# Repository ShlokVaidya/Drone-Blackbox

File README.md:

# Blackbox Drone Logger

Blackbox is a small drone telemetry logger built around a Seeed XIAO SAMD21. It sits on the drone, listens to the IMU and GPS, and writes everything to a microSD card so the flight data survives even if the airframe does not. lamo /j

I built it because I wanted a logger that felt like part of the drone, not an afterthought taped on the side. The whole point was to keep it compact, cheap enough to actually build.

## Media

### Full assembly

### PCB

### Top view

### Schematic

## What’s in the repo

- Journal: [JOURNAL.md](JOURNAL.md)
- Submission BOM: [BOM.csv](BOM.csv)
- Firmware: [firmware/](firmware/)

## Firmware

The firmware is a PlatformIO Arduino project for the XIAO SAMD21. It boots the IMU, listens for GPS sentences, and writes CSV rows to `/flight.csv` on the SD card.

---

### Onshape: [link](https://cad.onshape.com/documents/16e8a4c5b161029e325a2044/w/93c29fa5828ba80b97f8f047/e/c4410406f979bcbe292583a0?renderMode=0&uiState=6a0ef933e4e72416efe2d3e6)

---

## Hardware notes

- SD card chip select is routed to the XIAO D1 pin.
- I2C is on D4 and D5.
- GPS UART is on D6 and D7.
- SPI is on D8, D9, and D10.

## BOM

The submission BOM stays intentionally small. The total parts cost is about $45 before shipping, which keeps the project inside the cost target without turning it into a pile of extra parts.

| Name | Purpose | Quantity | Total Cost (USD) | Link | Distributor |
| --- | --- | ---: | ---: | --- | --- |
| LED Ring | for lighting | 1 | 0.50 | [product link](https://robu.in/product/8bit-ws2812-5050-rgb-led-built-full-color-driving-lights-circular-development-board/) | Robu |
| 6-axis IMU MPU6886 | Gyro and accelerometer | 1 | 9.80 | [product link](https://robu.in/product/m5stack-6-axis-imu-unit-mpu6886/) | Robu |
| NEO M8N | GPS coordinates | 1 | 10.00 | [product link](https://robu.in/product/apm2-5-ublox-neo-m8n-gps-module-gygpsv1-8m-3-5v-gygpsv5-neo-pixhawk-apm-ceramic-active-antenna/) | Robu |
| MicroSD Card Module | SD card module | 1 | 0.20 | [product link](https://www.robu.in/product/mini-micro-sd-card-reader-module/) | Robu |
| 3.7v 2500mah Battery | Battery | 1 | 6.50 | [product link](https://robu.in/product/wly104050-2500mah-3-7v-single-cell-rechargeable-lipo-battery/) | Robu |
| PCB | PCB | 1 | 10.00 | [product link](https://robu.in/) | Robu |
| XIAO SAMD21 | Microcontroller | 1 | 8.00 | [product link](https://robu.in/product/seeedstudio-seeeduino-xiao-pre-soldered/) | Robu |

Happy shipping : )

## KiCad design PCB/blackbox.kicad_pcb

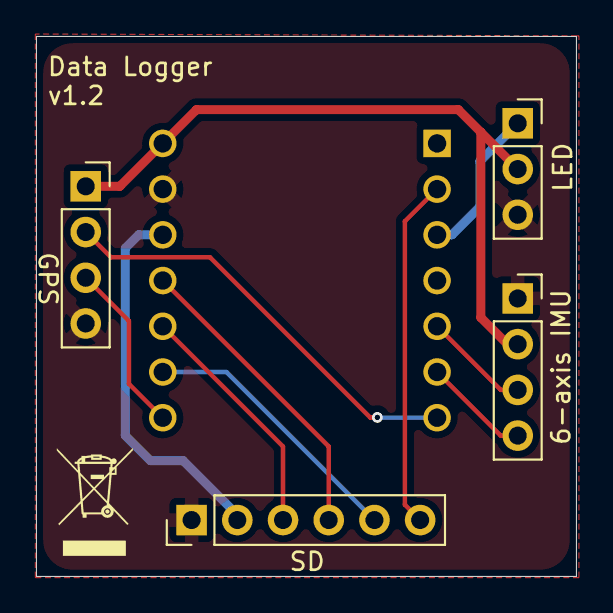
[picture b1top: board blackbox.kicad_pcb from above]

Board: 2 copper layers, 30.0 x 30.0 mm, 5 parts (1 on the bottom side), 12 nets.

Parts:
6-axis IMU: Gyro Socket; PinSocket_1x04_P2.54mm_Vertical
GPS: GPS Socket; PinSocket_1x04_P2.54mm_Vertical
LED: 8 Bit LED Ring; PinSocket_1x03_P2.54mm_Vertical
SAMD21: SEEED XIAO SAMD21; SAMD21
SD: SD Card Socket; PinHeader_1x06_P2.54mm_Vertical

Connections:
+3V3: SAMD21.12 (3V3), SD.2 (Pin_2_2)
+5V: 6-axis IMU.2, GPS.1, LED.2, SAMD21.14 (5V)
/CS: SAMD21.2 (PA4_A1_D1), SD.6 (Pin_6_6)
/LED: LED.1, SAMD21.3 (PA10_A2_D2)
/MISO: SAMD21.10 (PA5_A9_D9_MISO), SD.x (Pin_3_3)
/MOSI: SAMD21.11 (PA6_A10_D10_MOSI), SD.4 (Pin_4_4)
/RX: GPS.3, SAMD21.8 (PB09_A7_D7_RX)
/SCK: SAMD21.9 (PA7_A8_D8_SCK), SD.5 (Pin_5_5)
/SCL: 6-axis IMU.4, SAMD21.6 (PA9_A5_D5_SCL)
/SDA: 6-axis IMU.3, SAMD21.5 (PA8_A4_D4_SDA)
/TX: GPS.2, SAMD21.7 (PB08_A6_D6_TX)
GND: 6-axis IMU.1, GPS.4, LED.3, SAMD21.13 (GND), SD.1 (Pin_1_1)

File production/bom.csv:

Designator,Footprint,Quantity,Value,LCSC Part #
6-AXIS IMU,PinSocket_1x04_P2.54mm_Vertical,1,Gyro Socket,
GPS,PinSocket_1x04_P2.54mm_Vertical,1,GPS Socket,
LED,PinSocket_1x03_P2.54mm_Vertical,1,8 Bit LED Ring,
SAMD21,SAMD21,1,SEEED XIAO SAMD21,
SD,PinHeader_1x06_P2.54mm_Vertical,1,SD Card Socket,

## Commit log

2026-05-21 v1.2
2026-05-21 v1.2.2
2026-05-21 v1.2.3
2026-05-21 v1.2.4
